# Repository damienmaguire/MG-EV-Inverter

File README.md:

# MG-EV-Inverter
Reverse engineering of the drive motor and inverter used in MG Electric Vehicles.

The drive unit here is from a 2022 MG ZS EV Right hand drive. 

First look : https://vimeo.com/929258328

IGBT Module : FS820R08A6P2B

Gate driver : MC33GD3100EK

One current sensor per phase. 5V supply, 2.5V at zero current anlog output.

Isolated gate power supplies provided from a common 30VDC primary supply , a pair of 5V at 132KHz and 42% duty signals to a mosfet driver. Transformers are Epcos A213721495C.

HV Voltage sensing is achived using the external ADC channel of the Low3 gate driver and transmitted via spi.

The three IGBT temp sensors are fed into the relevant high side drivers. Temp is sensed using the external ADC channel of the  three high side gate drivers and transmitted via spi.

The OEM logic board communicates with all 6 gate drive chips via SPI at a clock rate of 1.7MHz. Data is in 16 bit format with an 8 bit crc and sent/received as 24 bit packets.
Sadly , NXP want an NDA to allow access to the SPI data for this device. As this would then tie me down from sharing the data I will not be going this route. Instead, we'll use reverse engineering and open
information to discern the data formatting.

Freely available information has been found here :

https://community.nxp.com/t5/Other-NXP-Products/MC33GD3100-daisy-chain/td-p/1309335

and

https://community.nxp.com/t5/Power-Management/CRC-seed-value-for-MC33GD3100/m-p/1677961

and

https://community.nxp.com/t5/Motor-Control-and-Smart-Energy/GD3160-SPI-Example-code-Question/m-p/1780583

A series of SPI logic analyser captures are now here on the repo. Files are in Saleae Logic 2 format which my be freely downloaded here : https://www.saleae.com/pages/downloads

An Openinverter logic board replacement is currently being designed to allow this drive unit to be used unrestricted. Design files will be in Kicad format : https://www.kicad.org/

The external power and signal connector is a Molex 500762-1001 available from Mouser : https://www.mouser.ie/ProductDetail/538-500762-1001

A pre wired 48 way plug to fit this is available from AliExpress : 
https://www.aliexpress.com/item/1005004818455812.html

The logic board to power board connector is a ERNI 063210-E available from Mouser : https://www.mouser.ie/ProductDetail/305-063210

The motor resolver and temp sensor connector is a TE 1897462-2 available from Mouser : https://www.mouser.ie/ProductDetail/571-1897462-2
Pins : https://www.mouser.ie/ProductDetail/571-7-1452656-3-CT

Gate driver signals are 5V level. One active low fault / INT line for high and low sides.

HV Connector may be Yonguui Metal Housing Connector-YG998C

V2 Logic board now undergoing testing.

Now working in closed loop FOC control with V2 logic board : https://vimeo.com/1032344714

Added 3D printable HV connector replacement. Also available on Printables : https://www.printables.com/model/1100211-mg-ev-drive-unit-high-voltage-connector

16/11/25 : Added all design and production files for the current V2 logic board. Files in Kicad 9 format. Happy MG spinning!

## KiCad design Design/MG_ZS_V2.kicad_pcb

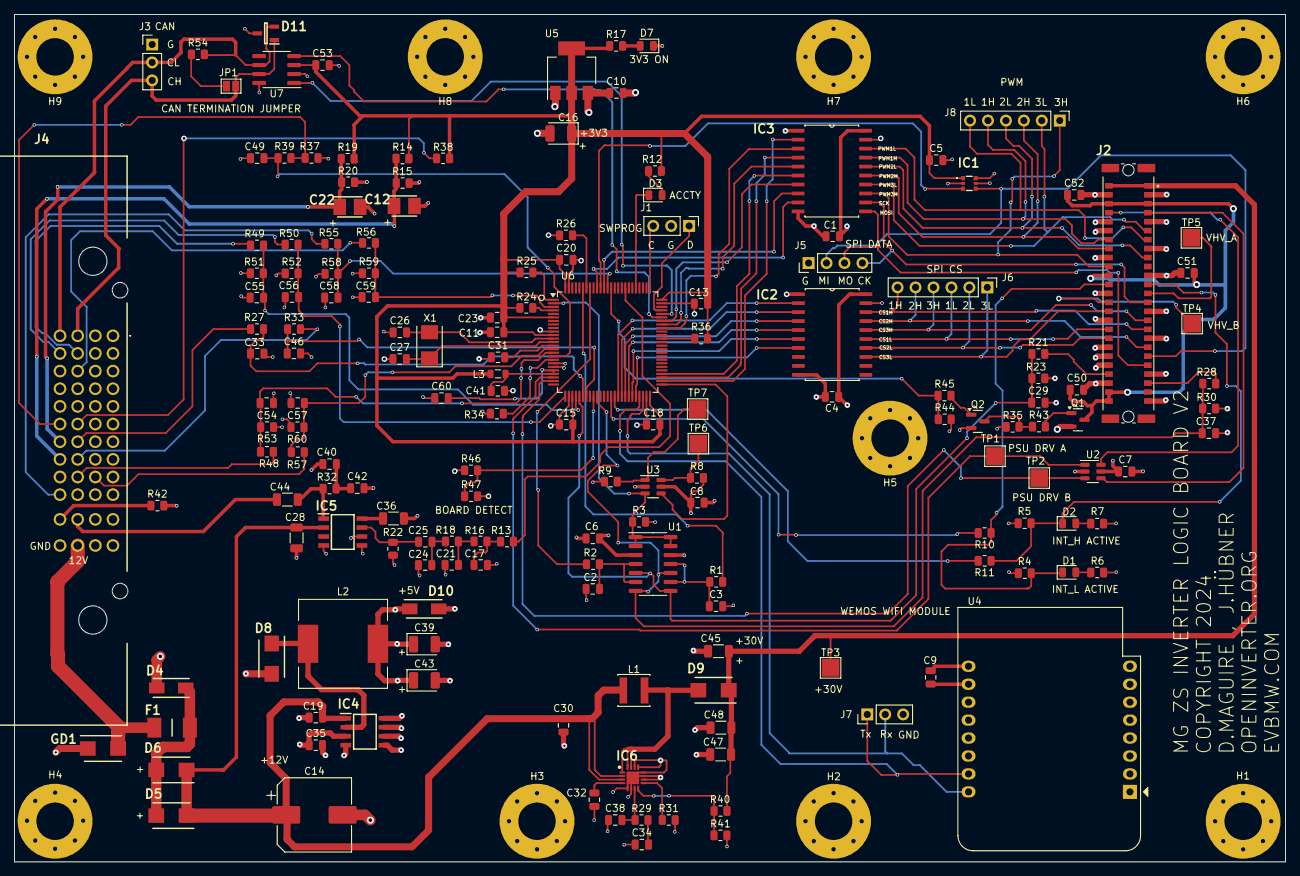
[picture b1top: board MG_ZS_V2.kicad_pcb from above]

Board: 4 copper layers, 180.0 x 120.0 mm, 177 parts (0 on the bottom side), 126 nets.

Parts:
C1, C2, C3, C4, C5, C6, C7, C8, C13, C15, C18, C19, C20, C23, C30, C35, C49, C50, C51, C52, C54, C55, C56, C57, C58, C59: 1uF; C_0805_2012Metric
C9, C10, C11, C41: 10uF; C_0805_2012Metric
C12, C22: 100uF 6.3V; CAPPM3528X210N
C14: 470uF 25V; CP_Elec_10x10
C16, C39, C43: 100uF 6.3V; CP_EIA-3528-15_AVX-H
C17, C21, C24, C25, C40, C42: 22nF; C_0805_2012Metric
C26, C27: 22pF; C_0805_2012Metric
C28, C36, C44: 10uF; C_1206_3216Metric
C29, C33, C37, C46: 1nF; C_0805_2012Metric
C31, C34, C53, C60: 100nF; C_0805_2012Metric
C32: 0.047uF; C_0805_2012Metric
C38: 100pF; C_0805_2012Metric
C45, C47, C48: 4.7uF; C_1206_3216Metric
D1: INTL LED; LED_0805_2012Metric
D2: INTH LED; LED_0805_2012Metric
D3: LED; LED_0805_2012Metric
D4: SMAJ18CA; DIONM5127X229N
D5, D6, D8, D9: SS54B; DIOM5336X244N
D7: 3V3 LED; LED_0805_2012Metric
D10: SMAJ7.0A; DIOM5026X229N
D11: ESDCAN01-2BLY; SOT95P255X150-3N
F1: JFC2410-0500TS; FUSC6126X280N
GD1: 2051-09-SM-RPLF; DIOM5336X244N
H1, H2, H3, H4, H5, H6, H7, H8, H9: MountingHole; MountingHole_5.3mm_M5_Pad_Via
IC1: 74LVCH1T45GW,125; 74LVCH1T45GW125
IC2, IC3: 74HCT245D,653; SOIC127P1032X265-20N
IC4: XL1509-5.0E1; SOIC127P600X175-8N
IC5: TDA2822D013TR; SOIC127P600X175-8N
IC6: TPS55340RTER; QFN50P300X300X80-17N-D
J1: M032.54MM; PinHeader_1x03_P2.54mm_Vertical
J2: 063210
J3: CAN MON; PinHeader_1x03_P2.54mm_Vertical
J4: 500762-1001; 5007621001
J5: Conn_01x04_Pin; PinHeader_1x04_P2.54mm_Vertical
J6, J8: Conn_01x06_Pin; PinHeader_1x06_P2.54mm_Vertical
J7: Conn_01x03_Pin; PinHeader_1x03_P2.54mm_Vertical
JP1: SolderJumper_2_Open; SolderJumper-2_P1.3mm_Open_Pad1.0x1.5mm
L1: 10uH; L_Sunlord_SWPA4030S
L2: 68uH; L_12x12mm_H8mm
L3: 10uH; L_0805_2012Metric
Q1: SL2301; SOT-23
Q2: MMBT3904; SOT-23
R1, R2, R13, R22, R27, R32, R33, R35, R37, R38, R39, R41, R44: 10K; R_0805_2012Metric
R3, R4, R5, R8, R9, R26, R49, R50, R55, R56: 4K7; R_0805_2012Metric
R6, R7, R24, R25, R34, R36, R43, R45, R48, R53, R57, R60: 1K; R_0805_2012Metric
R10, R11, R42: 0R; R_0805_2012Metric
R12, R29: 330R; R_0805_2012Metric
R14, R15, R19, R20: 220R; R_0805_2012Metric
R16, R18: 3K3; R_0805_2012Metric
R17: 680R; R_0805_2012Metric
R21, R28: 6K2; R_0805_2012Metric
R23, R30: 3K6; R_0805_2012Metric
R31: 78.7K; R_0805_2012Metric
R40: 237K; R_0805_2012Metric
R46: 47K; R_0805_2012Metric
R47: 5K1; R_0805_2012Metric
R51, R52, R58, R59: 1K5; R_0805_2012Metric
R54: 120R; R_0805_2012Metric
TP1, TP2, TP3, TP4, TP5, TP6, TP7: TestPoint; TestPoint_Pad_2.5x2.5mm
U1: LM2901; SOIC-14_3.9x8.7mm_P1.27mm
U2: 74LVC2G34; SOT-23-6
U3: 74LVC1G10; SOT-23-6
U4: WeMos_D1_mini; WEMOS_D1_mini_light
U5: AMS1117-3.3; SOT-223-3_TabPin2
U6: STM32F103VCTx; LQFP-100_14x14mm_P0.5mm
U7: SN65HVD230; SOIC-8_3.9x4.9mm_P1.27mm
X1: X50328MSB2GI; Crystal_SMD_5032-2Pin_5.0x3.2mm

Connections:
5V_CTRL: R44.1, R45.1, U6.87 (PD6)
+3.3VA: C41.2, C60.2, L3.2, U6.21 (VREF+), U6.22 (VDDA)
+3V3: C5.1, C11.2, C13.1, C15.1, C16.1, C18.1, C20.1, C23.1, C53.1, IC1.1 (VCC(A)), L3.1, R12.1, R14.2, R17.1, R19.2, R24.1, R25.1, R36.1, R38.1, U5.2 (VO), U6.6 (VBAT), U6.11 (VDD), U6.28 (VDD), U6.50 (VDD), U6.75 (VDD), U6.100 (VDD), U7.3 (VCC)
+5V: C1.1, C4.1, C6.1, C7.1, C8.1, C9.1, C10.1, C35.1, C39.1, C43.1, D10.1, IC1.6 (VCC(B)), IC2.1 (DIR), IC2.20 (VCC), IC3.1 (DIR), IC3.20 (VCC), IC4.3 (FEEDBACK), J4.J1, L2.2, Q1.2, R3.2, R4.2, R5.2, R6.1, R7.1, R8.2, R9.2, R35.2, R46.1, U1.3 (V+), U2.5 (VCC), U3.5 (VCC), U4.9 (5V), U5.3 (VI)
+5VP: C50.1, C51.1, C52.1, J2.A3, J2.B3, J2.B11, J2.B24, J2.B25, Q1.3
+12P: F1.1, GD1.2, J4.M3
+12V: C14.1, C19.1, C28.2, C30.1, D5.1, D6.1, IC4.1 (VIN), IC5.2 (SUPPLY_VOLTAGE), IC6.2 (VIN), IC6.3 (EN), L1.1
+30V: C45.1, C47.1, C48.1, D9.1, J2.A1, J2.B1, R40.1, TP3.1
ACCEL1: J4.J2, R57.2
ACCEL2: J4.J3, R48.2
BRAKE: J4.C3, R56.2
BRAKE_IN: C59.1, R56.1, R59.2, U6.3 (PE4)
CANH: D11.1, J3.3, J4.A3, JP1.2 (B), U7.7 (CANH)
CANL: D11.2, J3.2, J4.A4, R54.2, U7.6 (CANL)
CAN_RX: U6.70 (PA11), U7.4 (R)
CAN_TX: U6.71 (PA12), U7.1 (D)
COSA: C12.1, J4.H4, R14.1, R15.2
COSB: J4.H3, R33.2
CS1_HI: IC2.2 (A0), U6.41 (PE10)
CS1_LO: IC2.5 (A3), U6.44 (PE13)
CS2_HI: IC2.3 (A1), U6.42 (PE11)
CS2_LO: IC2.6 (A4), U6.45 (PE14)
CS3_HI: IC2.4 (A2), U6.43 (PE12)
CS3_LO: IC2.7 (A5), U6.46 (PE15)
CS_1H: IC2.18 (B0), J2.A17, J6.6
CS_1L: IC2.15 (B3), J2.B17, J6.3
CS_2H: IC2.17 (B1), J2.A19, J6.5
CS_2L: IC2.14 (B4), J2.B18, J6.2
CS_3H: IC2.16 (B2), J2.A16, J6.4
CS_3L: IC2.13 (B5), J2.B15, J6.1
EMCYSTOP_IN: R36.2, U6.64 (PC7)
ENC_A: C33.1, R27.1, U6.31 (PA6)
ENC_B: C46.1, R33.1, U6.32 (PA7)
EXCA: C44.2, J4.L3
EXCB: J4.L4, R42.1
EXC_OUT: R13.2, U6.83 (PD2)
FORW_IN: J4.B3, R49.2
FWD_IN: C55.1, R49.1, R51.2, U6.29 (PA4)
GATE_PSUA: TP1.1, U2.1, U6.23 (PA0)
GATE_PSUB: TP2.1, U2.3, U6.24 (PA1)
GND: C1.2, C2.2, C3.2, C4.2, C5.2, C6.2, C7.2, C8.2, C9.2, C10.2, C11.1, C12.2, C13.2, C14.2, C15.2, C16.2, C17.2, C18.2, C19.2, C20.2, C21.2, C22.2, C23.2, C24.2, C26.1, C27.1, C28.1, C29.2, C30.2, C31.1, C32.2, C33.2, C34.1, C35.2, C36.1, C37.2, C38.1, C39.2, C40.2, C41.1, C42.2, C43.2, C45.2, C46.2, C47.2, C48.2, C49.2, C50.2, C51.2, C52.2, C53.2, C54.2, C55.2, C56.2, C57.2, C58.2, C59.2, C60.1, D4.2, D7.1 (K), D8.2, D10.2, D11.3, GD1.1, H1.1, H2.1, H3.1, H4.1, H5.1, H6.1, H7.1, H8.1, H9.1, IC1.2 (GND), IC1.5 (DIR), IC2.10 (GND), IC2.19 (~OE), IC3.10 (GND), IC3.19 (~OE), IC4.4 (ON/OFF), IC4.5 (GND_1), IC4.6 (GND_2), IC4.7 (GND_3), IC4.8 (GND_4), IC5.4 (GROUND), IC5.5 (INPUT-(2)), IC5.6 (INPUT+(2)), IC6.5 (SYNC), IC6.6 (AGND), IC6.10 (NC_1), IC6.11 (PGND_1), IC6.12 (PGND_2), IC6.13 (PGND_3), IC6.14 (NC_2), IC6.17 (POWERPAD), J1.2, J2.A2, J2.A5, J2.A8, J2.A11, J2.A15, J2.A18, J2.A22, J2.A25, J2.B2, J2.B5, J2.B6, J2.B9, J2.B13, J2.B16, J2.B19, J2.B20, J2.B21, J2.B23, J3.1, J4.J4, J4.K3, J4.M4, J5.1, J7.3, Q2.2 (E), R15.1, R20.1, R22.1, R23.1, R26.1, R30.1, R31.2, R34.1, R37.1, R41.2, R42.2, R44.2, R47.2, R51.1, R52.1, R53.1, R58.1, R59.1, R60.1, U1.12 (V-), U2.2 (GND), U3.2 (GND), U4.10 (GND), U5.1 (GND), U6.10 (VSS), U6.19 (VSSA), U6.20 (VREF-), U6.27 (VSS), U6.49 (VSS), U6.74 (VSS), U6.99 (VSS), U7.2 (GND), U7.8 (Rs)
IL1: C29.1, R21.1, R23.2, U1.5 (+), U1.8 (-), U6.30 (PA5)
IL1_IN: J2.B22, R21.2
IL2: C37.1, R28.1, R30.2, U1.7 (+), U1.10 (-), U6.35 (PB0)
IL2_IN: J2.A23, R28.2
INA: J2.B4, U2.6
INB: J2.A4, U2.4
INTA_IN: R11.2, U6.40 (PE9)
INTB_H: D2.1 (K), J2.A12, R5.1, R11.1
INTB_IN: R10.2, U6.39 (PE8)
INTB_L: D1.1 (K), J2.B12, R4.1, R10.1
LED_OUT: D3.1 (K), U6.80 (PC12)
MISO: IC1.4 (B), J2.A20, J5.2
MOSI: IC3.11 (B7), J2.A21, J5.3
MOT_NTC1: J4.F3, R38.2
MOT_NTC2: J4.F4, R37.2, R39.2
MPROT_IN: R24.2, U6.4 (PE5)
unnamed: C17.1, R13.1, R16.2
unnamed: C21.1, R16.1, R18.2
unnamed: C24.1, C25.1, R18.1
unnamed: C34.2, R29.2
unnamed: C40.1, C42.1, R32.1
unnamed: D1.2 (A), R6.2
unnamed: D2.2 (A), R7.2
unnamed: D3.2 (A), R12.2
unnamed: D4.1, D5.2, D6.2, F1.2
unnamed: D7.2 (A), R17.2
unnamed: D8.1, IC4.2 (OUTPUT), L2.1
unnamed: C25.2, IC5.7 (INPUT-(1)_1), R22.2
unnamed: C36.2, IC5.8 (INPUT-(1)_2)
unnamed: C44.1, IC5.1 (OUTPUT(1)), R32.2
unnamed: C38.2, IC6.7 (COMP), R29.1
unnamed: IC6.8 (FB), R40.2, R41.1
unnamed: IC6.9 (FREQ), R31.1
unnamed: C32.1, IC6.4 (SS)
unnamed: D9.2, IC6.1 (SW_1), IC6.15 (SW_2), IC6.16 (SW_3), L1.2
unnamed: JP1.1 (A), R54.1
unnamed: Q1.1, R43.2
unnamed: Q2.1 (B), R45.2
unnamed: Q2.3 (C), R35.1, R43.1
unnamed: R8.1, TP6.1, U3.6
unnamed: R9.1, TP7.1, U3.1
unnamed: C2.1, R2.1, U1.4 (-), U1.6 (-)
unnamed: C3.1, R1.1, U1.9 (+), U1.11 (+)
unnamed: R26.2, U6.94 (BOOT0)
unnamed: C31.2, U6.14 (NRST)
unnamed: C26.2, U6.12 (OSC_IN), X1.2
unnamed: C27.2, U6.13 (OSC_OUT), X1.1
unnamed: R46.2, R47.1, U6.34 (PC5)
OCURLIM_NEG: R2.2, U6.93 (PB7)
OCURLIM_POS: R1.2, U6.95 (PB8)
OCUR_IN: R3.1, U1.1, U1.2, U1.13, U1.14, U3.3, U6.2 (PE3)
PWM1H: IC3.17 (B1), J2.B7, J8.5
PWM1L: IC3.18 (B0), J2.A7, J8.6
PWM1_N: IC3.2 (A0), U6.52 (PB13)
PWM1_P: IC3.3 (A1), U6.67 (PA8)
PWM2H: IC3.15 (B3), J2.B8, J8.3
PWM2L: IC3.16 (B2), J2.A9, J8.4
PWM2_N: IC3.4 (A2), U6.53 (PB14)
PWM2_P: IC3.5 (A3), U6.68 (PA9)
PWM3H: IC3.13 (B5), J2.B10, J8.1
PWM3L: IC3.14 (B4), J2.A6, J8.2
PWM3_N: IC3.6 (A4), U6.54 (PB15)
PWM3_P: IC3.7 (A5), U6.69 (PA10)
PWM_INHIBIT: U3.4, U6.51 (PB12)
REVER_IN: J4.B4, R50.2
REV_IN: C56.1, R50.1, R52.2, U6.26 (PA3)
SCK: IC3.12 (B6), J2.A14, J5.4
SINA: C22.1, J4.G4, R19.1, R20.2
SINB: J4.G3, R27.2
SPI1_MISO: IC1.3 (A), U6.90 (PB4)
SPI1_MOSI: IC3.9 (A7), U6.91 (PB5)
SPI1_SCK: IC3.8 (A6), U6.89 (PB3)
START: J4.K4, R55.2
START_IN: C58.1, R55.1, R58.2, U6.88 (PD7)
SWCLK: J1.3, U6.76 (PA14)
SWDAT: J1.1, U6.72 (PA13)
THROTTLE1: C57.1, R57.1, R60.2, U6.15 (PC0)
THROTTLE2: C54.1, R48.1, R53.2, U6.16 (PC1)
TMPM: C49.1, R39.1, U6.17 (PC2)
UDCIN: R34.2, U6.18 (PC3)
USART_RX: J7.2, U4.16 (TX), U6.48 (PB11)
USART_TX: J7.1, U4.15 (RX), U6.47 (PB10)
UVLO_IN: R25.2, U6.1 (PE2)
VHV_A: J2.A13, TP5.1
VHV_B: J2.B14, TP4.1

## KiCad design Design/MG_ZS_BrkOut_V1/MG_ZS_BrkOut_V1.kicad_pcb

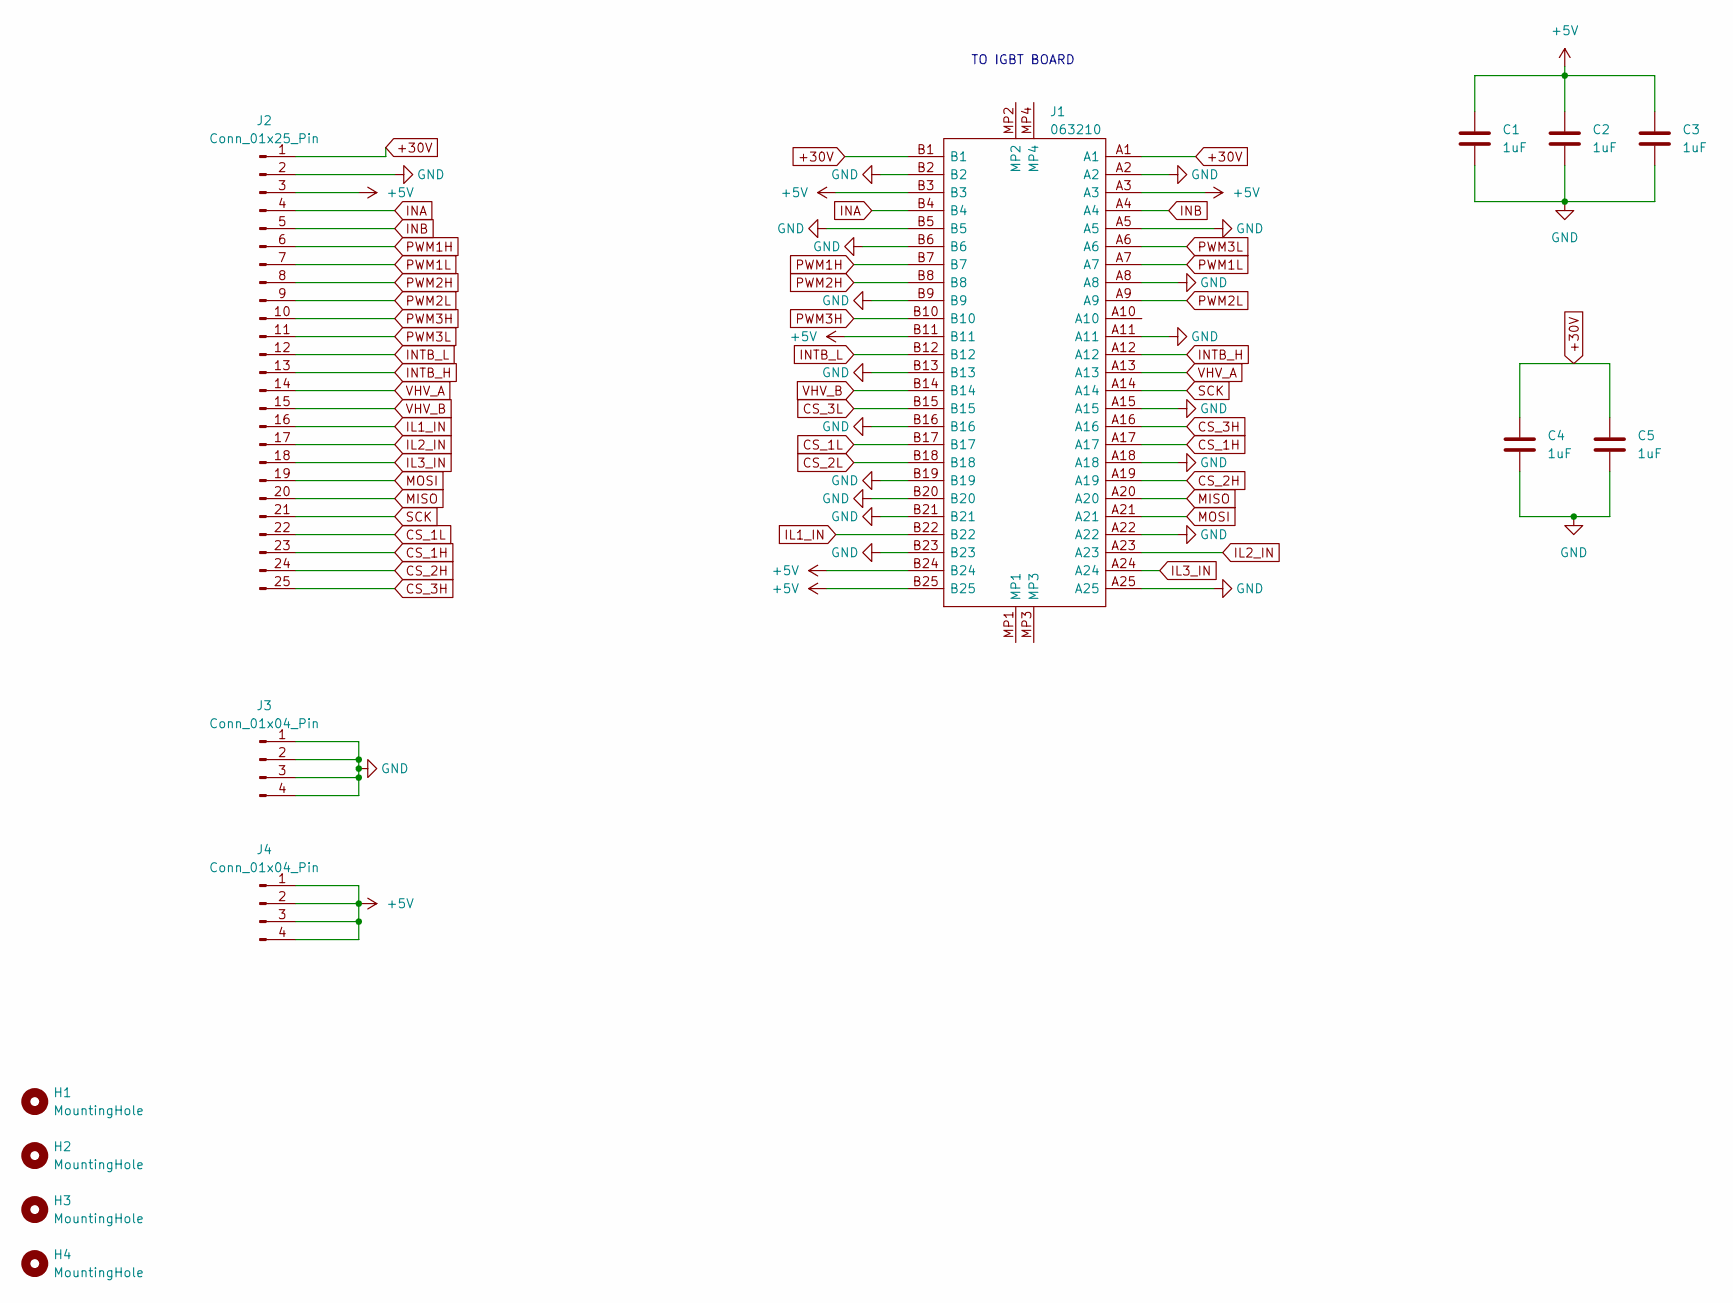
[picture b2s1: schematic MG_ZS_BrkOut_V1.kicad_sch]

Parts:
C1, C2, C3, C4, C5: 1uF; C_0805_2012Metric
H1, H2, H3, H4: MountingHole; MountingHole_4.3mm_M4_ISO7380_Pad_TopBottom
J1: 063210; Manufacturer_Part_Number 063210; Mouser Part Number 305-063210
J2: Conn_01x25_Pin; PinHeader_1x25_P2.54mm_Vertical
J3, J4: Conn_01x04_Pin; PinHeader_1x04_P2.54mm_Vertical

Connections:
+5V: C1.1, C2.1, C3.1, J1.A3, J1.B3, J1.B11, J1.B24, J1.B25, J2.3, J4.1, J4.2, J4.3, J4.4
+30V: C4.1, C5.1, J1.A1, J1.B1, J2.1
CS_1H: J1.A17, J2.23
CS_1L: J1.B17, J2.22
CS_2H: J1.A19, J2.24
CS_2L: J1.B18
CS_3H: J1.A16, J2.25
CS_3L: J1.B15
GND: C1.2, C2.2, C3.2, C4.2, C5.2, J1.A2, J1.A5, J1.A8, J1.A11, J1.A15, J1.A18, J1.A22, J1.A25, J1.B2, J1.B5, J1.B6, J1.B9, J1.B13, J1.B16, J1.B19, J1.B20, J1.B21, J1.B23, J2.2, J3.1, J3.2, J3.3, J3.4
IL1_IN: J1.B22, J2.16
IL2_IN: J1.A23, J2.17
IL3_IN: J1.A24, J2.18
INA: J1.B4, J2.4
INB: J1.A4, J2.5
INTB_H: J1.A12, J2.13
INTB_L: J1.B12, J2.12
MISO: J1.A20, J2.20
MOSI: J1.A21, J2.19
PWM1H: J1.B7, J2.6
PWM1L: J1.A7, J2.7
PWM2H: J1.B8, J2.8
PWM2L: J1.A9, J2.9
PWM3H: J1.B10, J2.10
PWM3L: J1.A6, J2.11
SCK: J1.A14, J2.21
VHV_A: J1.A13, J2.14
VHV_B: J1.B14, J2.15

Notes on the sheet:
TO IGBT BOARD

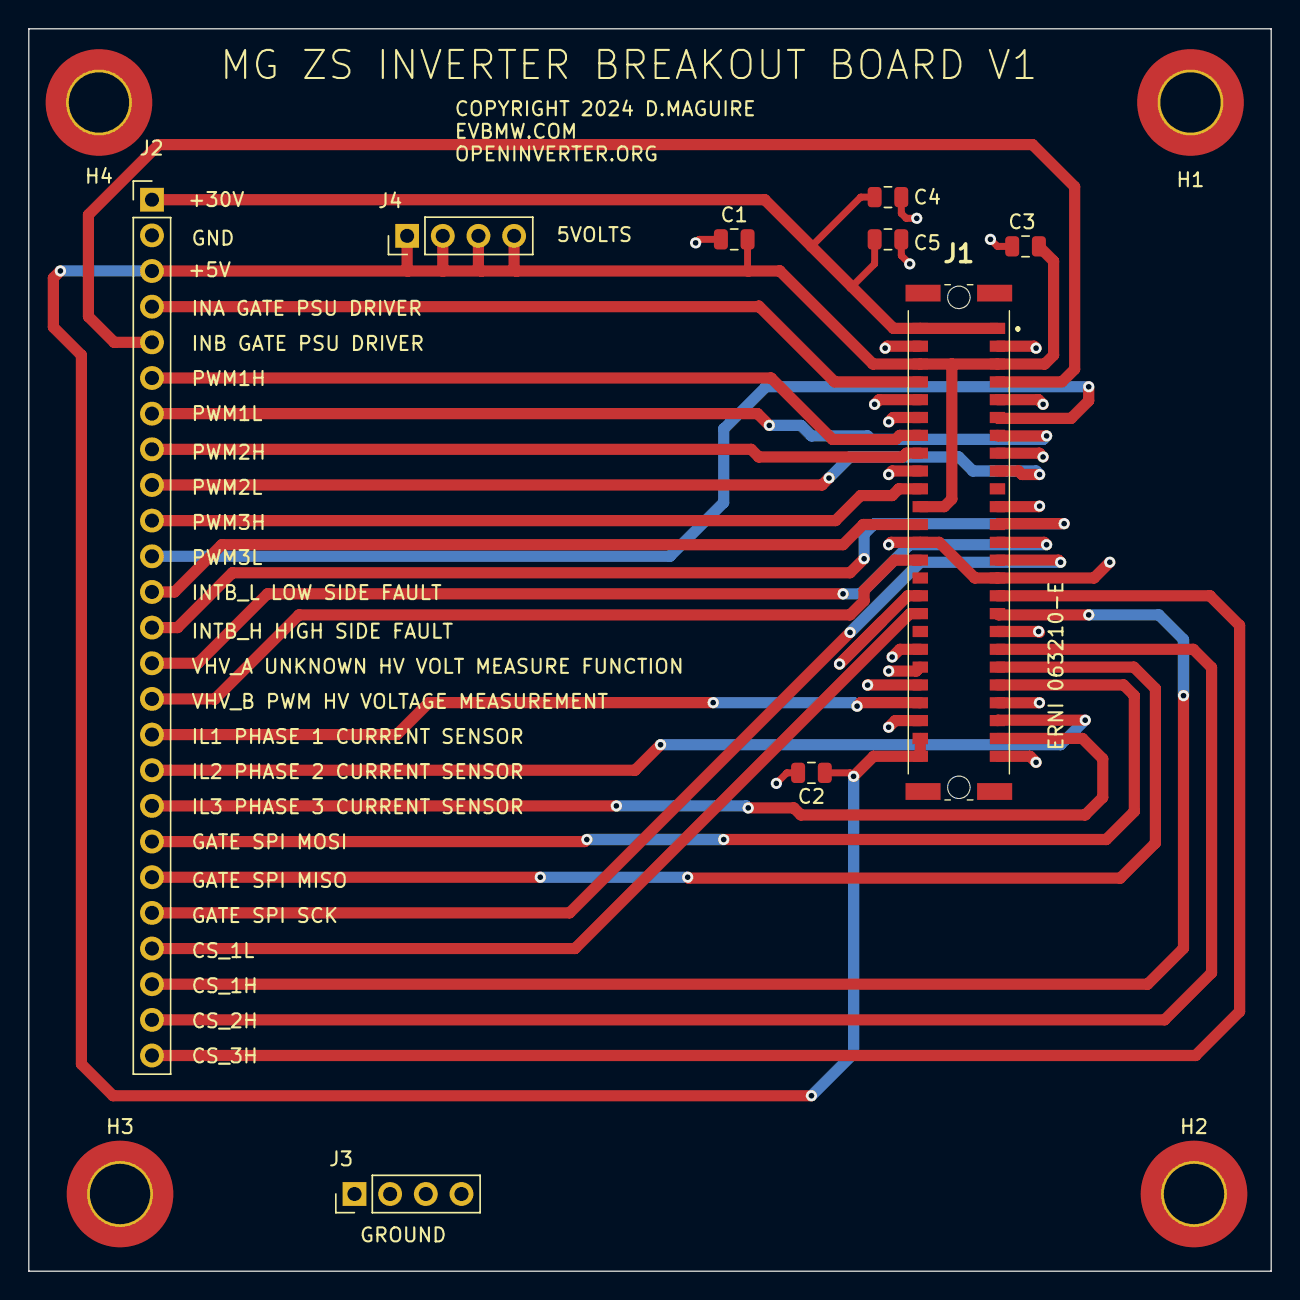
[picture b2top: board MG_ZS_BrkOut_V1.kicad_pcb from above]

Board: 2 copper layers, 88.5 x 88.5 mm, 13 parts (0 on the bottom side), 25 nets.

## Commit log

2024-04-05 Add breakout board gerber
2024-10-24 Add V2 Logic Board Schematic
2024-11-14 Add pinouts
2024-11-27 Add V2 Schematic and board layout
2024-11-27 Add V2 3D board view
2024-12-07 Add V2 Logic Board Gerber Files
2024-12-07 Add stl file for M20 gland plate
2025-11-16 Add V2 Design

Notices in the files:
Design/MG_ZS_BrkOut_V1/MG_ZS_BrkOut_V1.kicad_pcb:
COPYRIGHT 2024 D.MAGUIRE
